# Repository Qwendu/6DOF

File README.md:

# 6DOF
Six degrees of Freedom Controller to facilitate intuitive movement in 3 Dimensional Space (Translations and Roatations).

See my writeup/ more detailed project description here:
[Project Description Page](https://n.ethz.ch/~spfeiler/Projects/6DOF/index.html)

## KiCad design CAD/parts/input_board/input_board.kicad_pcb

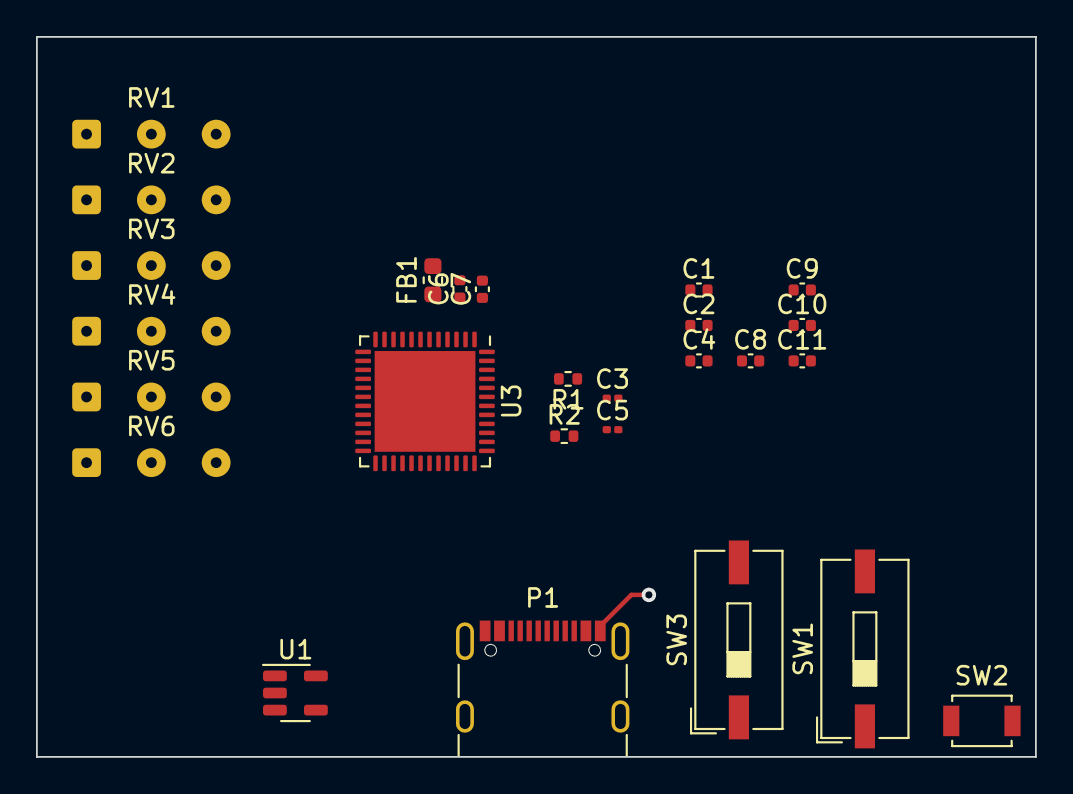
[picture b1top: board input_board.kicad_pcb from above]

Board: 2 copper layers, 55.5 x 40.0 mm, 26 parts (0 on the bottom side), 16 nets.

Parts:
C1, C2, C4: 100n; C_0402_1005Metric
C3, C5: 4.7u; C_0201_0603Metric
C6: 10n; C_0402_1005Metric
C7, C9, C11: 1u; C_0402_1005Metric
C8: C?; C_0402_1005Metric
C10: 0.1u; C_0402_1005Metric
FB1: 120R; L_0603_1608Metric
P1: USB_C_Plug_USB2.0; USB_C_Receptacle_GCT_USB4105-xx-A_16P_TopMnt_Horizontal
R1: 1k5; R_0402_1005Metric
R2: 10k; R_0402_1005Metric
RV1, RV2, RV3, RV4, RV5, RV6: 10k; SolderWire-0.1sqmm_1x03_P3.6mm_D0.4mm_OD1mm
SW1: Power Switch; SW_DIP_SPSTx01_Slide_9.78x4.72mm_W8.61mm_P2.54mm
SW2: RST; SW_SPST_B3U-1000P
SW3: BOOT Select; SW_DIP_SPSTx01_Slide_9.78x4.72mm_W8.61mm_P2.54mm
U1: NCV8114ASN330T1G; TSOT-23-5
U3: STM32F042C6Ux; QFN-48-1EP_7x7mm_P0.5mm_EP5.6x5.6mm

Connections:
/BOOT0: R2.2, U3.44 (PF11)
/USB_D+: P1.A6 (D+), R1.1, U3.33 (PA12)
/USB_D-: P1.A7 (D-), U3.32 (PA11)
/X_Rot: RV4.2, U3.13 (PA3)
/X_Trans: RV1.2, U3.10 (PA0)
/Y_Rot: RV5.2, U3.14 (PA4)
/Y_Trans: RV2.2, U3.11 (PA1)
/Z_Rot: RV6.2, U3.15 (PA5)
/Z_Trans: RV3.2, U3.12 (PA2)
GND: C1.2, C2.2, C3.2, C4.2, C5.2, C6.2, C7.2, C8.2, C9.2, C10.2, C11.2, P1.A1 (GND), P1.A12 (GND), P1.B1 (GND), P1.B12 (GND), RV1.1, RV2.1, RV3.1, RV4.1, RV5.1, RV6.1, SW1.1 (A), SW2.1 (A), SW3.1 (A), U1.2 (GND), U3.8 (VSSA), U3.23 (VSS), U3.35 (VSS), U3.47 (VSS), U3.49 (VSS)
NRST: C10.1, SW2.2 (B), U3.7 (NRST)
unnamed: SW1.2 (B), U1.3 (EN)
unnamed: R2.1, SW3.2 (B)
VBUS: C8.1, P1.A4 (VBUS), P1.A9 (VBUS), P1.B4 (VBUS), P1.B9 (VBUS), U1.1 (IN)
VDD: C1.1, C2.1, C3.1, C4.1, C5.1, C9.1, C11.1, FB1.2, U1.5 (OUT), U3.1 (VBAT), U3.24 (VDD), U3.36 (VDDIO2), U3.48 (VDD)
VDDA: C6.1, C7.1, FB1.1, R1.2, RV1.3, RV2.3, RV3.3, RV4.3, RV5.3, RV6.3, U3.9 (VDDA)

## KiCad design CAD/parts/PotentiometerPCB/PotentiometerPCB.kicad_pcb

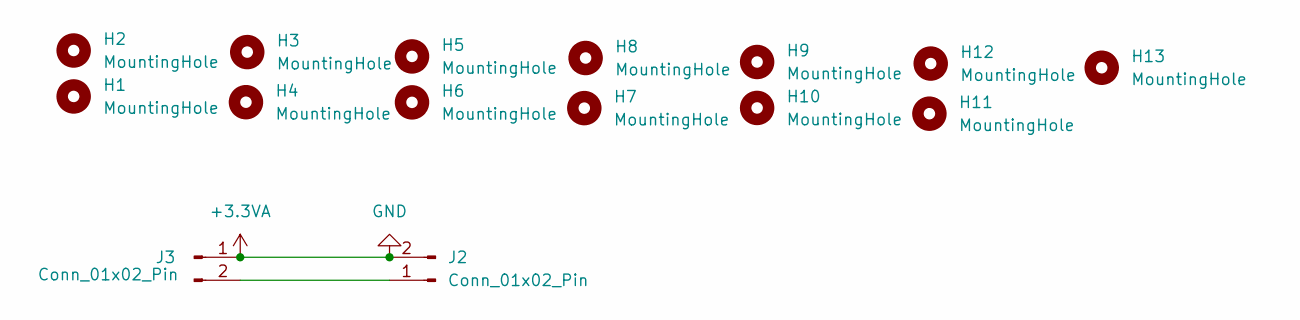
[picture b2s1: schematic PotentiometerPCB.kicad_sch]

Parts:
H1, H2, H3, H4, H5, H6, H7, H8, H9, H10, H11, H12, H13: MountingHole; MountingHole_3.2mm_M3
J2, J3: Conn_01x02_Pin; PinHeader_1x02_P1.00mm_Horizontal

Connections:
+3.3VA: J2.2, J3.1
unnamed: J2.1, J3.2

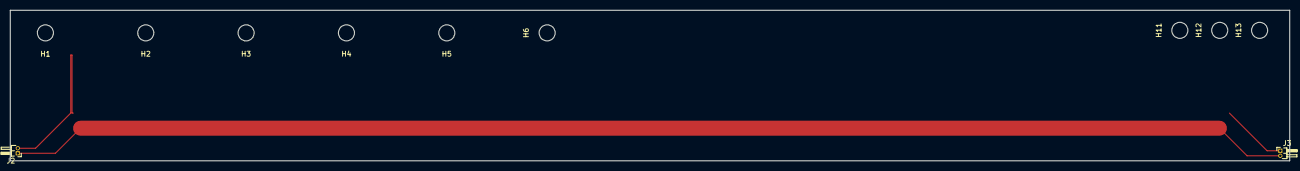
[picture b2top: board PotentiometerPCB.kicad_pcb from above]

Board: 2 copper layers, 255.0 x 30.0 mm, 15 parts (0 on the bottom side), 2 nets.

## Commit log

2022-09-08 Improvements
2023-04-28 Some programming
2023-07-17 Remoced OBJ files
2023-07-17 Starting the design doc
2023-09-23 Starting To redesign Parts for Better Assembly
2023-09-23 Slide Assembly
2023-09-23 Remove FCStd1 files
2023-09-23 First Assembly in version 7
2023-09-23 Skeletonized ZY Connector
2023-09-24 STL Files
2023-09-26 Added Omniball Connector
2023-09-26 Assembly for v7, Renaming of XZ to NormalConnecto because it can be used more generally
2023-09-26 v7 fin
2023-09-26 updated ideas
2023-09-30 MagnetoPot
2023-10-02 Slimming NormalConnector
2023-10-09 Manufacturing v8
2023-10-10 hci pitch
2023-10-13 PCB for Linear Connector
